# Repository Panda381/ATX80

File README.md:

# ATX80
ZX-80 computer clone with ATmega8 processor and with BASIC interpreter written in AVR assembler.

Last Update: 12/15/2021

open source

(c) Miroslav Nemecek
Panda38@seznam.cz

project home web page: http://www.breatharian.eu/hw/atx80/index_en.html

ATX80 on GitHub: https://github.com/Panda381/ATX80

License
-------
All of my software creations are distributed under the Unlicense
https://spdx.org/licenses/Unlicense.html,
and my hardware creations under the CC0 license
https://creativecommons.org/publicdomain/zero/1.0/legalcode.en.
You are free to use, modify, and distribute them for any purpose without having
to credit me as the author. The exception is content derived from third-party
sources. These third-party components are not covered by my Unlicense or CC0
licenses, but rather by the original license terms of their authors. These
components are marked in the code, and when using them, you must comply with
the terms of the original licenses.

Description
-----------
The ATX-80 is a microcomputer derived from the ZX-80, with an ATmega8 processor. It does not emulate code, but replaces the original computer with custom code with similar functionality in AVR assembly. It allows output of the video to a VGA monitor or to a PAL/NTSC television. BASIC programs can be stored in internal EEPROM, internal Flash or external EEPROM memory (32 memory slots) and also transferred between PC and memory. The advantages are easy construction and small size. It can be used as a small inexpensive computer for teaching basic BASIC programming. Includes 32 sample programs.

The original intent of the project was to create a computer with similar features and technical limitations as the original ZX-80. That is, a fully functional BASIC interpreter with only 1 KB of RAM and as close to 4 KB of ROM as possible. The project was also conceived as a study of the original ZX-80 BIOS ROM. It must be admitted that the original ZX-80 BIOS was an admirable creation. In addition to being very innovative, it was created with a high optimization of code size, and although this required a considerable amount of clarity in the flow of data between functions, the author maintained an overview of the code with minimal errors. I have tried to keep the functionality of the original code as accurate as possible and commented my code in detail, which can be a useful addition to explain the BIOS functionality. The ZX-80 BIOS is a very useful and informative study material and, despite its age, deserves more attention as an admirable work.

The ATmega8 processor was chosen to rewrite the code, which has 1 KB of RAM (the same limitation as the ZX-80) and 8 KB of Flash memory. Although the Flash memory is more than the original 4 KB, the code was about 40% longer after rewriting (AVR instructions are 16-bit) and additional functions were added, such as a more complex video generator, memory handling, 1 KB of internal Flash was used as a memory slot to store programs, so the 8 KB of memory was used efficiently.

The ATX-80 includes a keyboard of 40 micro switches. It can generate video for VGA monitor and also video in PAL and NTSC television standard via Cinch connector. It is powered by an external +5V source via USB connector (USB charger or computer connector). An external 32 KB EEPROM memory is used to store user BASIC programs, allowing 32 programs to be stored in 32 memory slots. In addition to the external EEPROM memory, one internal memory slot in the processor's Flash memory can be used to copy programs between different external EEPROM memories. The edited program is also automatically mirrored in the internal EEPROM memory. The internal EEPROM has a size of only 512 bytes, so some programs do not fit in it completely, but most programs are no larger than 512 bytes (RAM must be shared with variables and video memory) and for longer programs at least a larger part is backed up.

Advantages of the ATX-80 over the original ZX-80:
- VGA video output
- Image is generated while the program is running (FAST and SLOW modes can be used)
- Preservation of the edited program even after shutdown
- Saving programs to external EEPROM
- Autorepeat keys
- Function with memory information
- Higher program running speed
- Small size

Limitations of the ATX-80 compared to the original ZX-80:
- Cannot run programs in machine code (USR function is not functional)
- Memory cannot be increased by external memory
- Cannot connect additional devices via external bus
- The tape recorder cannot be used to store programs, only its own EEPROM memory can be used
- Generated image characters contain an extra 9th white bar (consequence of image generation by SPI port)

ZX-80 BIOS errors
-----------------
While studying the ZX-80 BIOS I came across a few minor bugs.

1) REM command error. The address of the REM routine should be L0849 instead of L084A. The error causes that giving the REM command without parameters (no text) will not execute the next line.

2) Error in the ED-EDIT routine - the following instructions should be in reverse order. The error can cause the computer to crash when writing a command when memory is full.

	JR NC,L03A7	; back to ED-COPY if not enough
			; room to fill edit line.
	POP HL		; restore program position.

3) The following error, although not apparent, is a potential risk when changing the compilation. At the beginning of the L03CB ED-EDIT routine, the initialization of register B to a value representing the number of lines to print is missing (a number of 2 or higher is needed). At this point, register B contains a value of 3 (derived from address L03CB), which is suitable, but recompiling from a different address could cause the bottom screen to stop printing. However, it is possible that the author deliberately omitted this instruction there, as part of the optimization.

Wiring diagram
--------------
The main processor is ATmega8. If necessary, it can be replaced by ATmega88, ATmega168 or ATmega328 processors, which are pin compatible. A different firmware code must be used, which is also provided in the download package. However, the larger memory of the higher processor types is not used.

The processor is driven by a 24 MHz crystal. This frequency is necessary to display the required resolution on a VGA monitor. Although the frequency of the crystal used lies above the limits declared by the manufacturer, in practice it has been found that practically all processors can handle such overclocking fine. Still, it is advisable to use a socket for the processor and try another piece of the processor in case of difficulties. Insufficient supply voltage may also be the cause of malfunction. The cutoff frequency of the processor is dependent on the power supply, a low supply voltage may cause the processor to not work properly with the crystal used.

The keyboard is wired in a 5x8 key matrix, with similar wiring to the original ZX-80, just with reverse current flow. When scanning the keyboard, signals COL1 to COL5 are wired as input (i.e., high impedance state) and only one of the COL signals is set as output with the LOW level. Signals ROW1 to ROW8 are connected as input with an internal pull-up resistor. When the keypad is scanned, one of the COL signals is activated to LOW level and the reading of the ROW signals detects the key pressed.

The MOSI output from the SPI generator is routed as a video signal to both the VGA connector and the CINCH connector for output to the TV. The output is assumed to be loaded with a 75 ohm input resistor, which will provide the required voltage level of 0.7V. The SYNC signal is the output from Timer1, which provides horizontal synchronization. Timer1 simultaneously triggers an interrupt to the video generator, which sends the video data through the SPI controller.

The VSYNC signal is only used in "old VGA display" mode. Otherwise, a CSYNC sync mix is normally generated at the SYNC output. The vertical signal is created in the sync mix by negating the horizontal sync signal. Most current VGA monitors support sync mix and work well in this mode. Only older VGA monitors require the use of a VSYNC signal as well. For most monitors, no difference between old/new VGA monitor modes should normally be observed.

The external EEPROM memory is connected via the TWI/I2C signals (SDA and SCL). A 32 KB 24LC256P memory is recommended as the most suitable type, which can hold 32 user programs (32 slots, where each slot is 1 KB in size). In addition to this, 24LC32 (4KB, i.e. 4 slots), 24LC64 (8 KB, i.e. 8 slots), 24LC128 (16 KB, i.e. 16 slots) and 24LC512 (64 KB, i.e. 64 slots) can also be used. The memories differ only in the number of available memory slots.

It is advisable to use a socket for the EEPROM memory so that it can be replaced with another one with different stored programs if necessary. Programs can be copied between memories using both the slot in the internal Flash memory and the included copy utility.

The EEPROM memories used contain a write-protect input pin. The ATX-80 does not provide for this, but a configuration jumper can be added to the board to enable or disable writing to the EEPROM memory and thus protect its contents against unwanted overwriting.

Note: The ATX-80 does not recognize the size of the attached EEPROM memory. It is up to the user to use the correct slot number. If you use a slot number outside the memory range, the slot number will be overwritten by modulo operations to another slot (EEPROM ignores unused higher address bits) and may inadvertently overwrite another stored program. For example, writing to slot 34 in a 32 KB memory will write to slot 2.

Note 2: It is assumed that the same hardware will be used for the planned ZX-81 clone, but a different processor with larger memory (probably ATmega328) will be used. Therefore, use a socket for the processor to make it easily replaceable.

Construction
------------
The ATX-80 is designed for a 100x75 mm single-sided PCB - partly because of the limitations of the freeware version of the Eagle editor, and partly because this is one of the dimensions of commonly sold photo-etch PCBs. I produce the PCB by printing the master in an inkjet printer on transparent film (gluing 2 printed master with adhesive for better coverage), illuminating with UV-LED field (10 minutes from a distance of 30 cm), exposing in potassium hydroxide and etching in ferric chloride.

Please note that in case of customised PCB production, it is necessary to check the definitions of the hole diameters in the template (I drilled the holes myself and therefore not verified).

A sticker with button labels is folded over the buttons. I printed it on regular paper on an inkjet printer, covered both sides with adhesive and then punched holes for the buttons with a 4 mm cut-out.

Programming and starting up
---------------------------
Set the fuses as follows:

ATmega8: low 0xEF (default 0xE1), high 0xC7 (default 0xD9)
ATmega88: low 0xF7 (default 0x62), high 0xD7 (default 0xDF), ext 0xFF (default 0xF9)
ATmega168: low 0xF7 (default 0x62), high 0xD7 (default 0xDF), ext 0xFF (default 0xF9)
ATmega328: low 0xF7 (default 0x62), high 0xD7 (default 0xD9), ext 0xFF (default 0xFF)

The fuses are set to map the boot loader to the smallest memory size (needed for writing to the internal flash memory), protect the internal EEPROM during programming, and fast external crystal.

If you connect a VGA monitor after programming the processor, you should see a basic white screen with a "K" cursor in the lower left corner. If this does not happen, a video mode other than the default VGA may be selected. To switch the video mode, hold down any of the buttons 1 through 4 on the keyboard while turning on the power:

- 1 + power supply: old VGA monitor (uses VSYNC signal)
- 2 + power supply: new VGA monitor (uses CSYNC sync mix)
- 3 + power supply: NTSC TV video mode (output via CINCH connector)
- 4 + power supply: PAL TV video mode (output via CINCH connector)

The selected configuration is stored in the last byte of the EEPROM memory for future use. If the video mode cannot be switched, you may have a short circuit on one of the buttons.

Be careful not to use the above operation to set the vieomode on a processor with a copy utility. It could inadvertently activate the programming of the external EEPROM.

You can check whether the processor is working without connecting the display. Insert the LED into the VGA connector between pins 14 (anode, long plus pin) and 10 (cathode, shorter minus pin). If you turn on video mode 1 (the old VGA monitor), the LED will light up (VSYNC signal is active), the LED will not light up for other video modes. Or you can plug the LED into the CINCH connector (anode to the pinhole, cathode to the shell) - if an image is being generated, the LED will light.

Programming EEPROM with sample programs
---------------------------------------
Uploading programs to EEPROM

After testing the basic functionality of the ATX-80, I recommend programming the connected external EEPROM memory. In the attachment you will find a set of utilities to load a set of 32 sample programs into the EEPROM. This requires either reprogramming the main processor or using another processor as a "copier".

In the utilities package there is a folder ATX80_Import, where you can find firmware (BIN files) for the copy processor, prepared for ATmega8/88/168/328 processors (the first number in the BIN file name indicates the processor). There are 3 sets of programs for each type of processor: slot 1 to 12, slot 13 to 24 and slot 25 to 32. The contents of the programs can be found in the utility package in the files Programs_1.txt, Programs_2.txt and Programs_3.txt. Alternatively, the program descriptions can be found in the Programs.txt file in the ATX-80 source code package.

The copy program does not use a display, but only an indicator LED to save memory. Insert it into the VGA connector on the VSYNC signal, between pins 14 (anode, long plus pin) and 10 (cathode, shorter minus pin).

Load the *_1.bin program with the first set of sample programs into the processor. The LED will flash rapidly to indicate that the processor is in a standby state. If you now press button 4 on the keypad, the LED will light steadily for a few seconds to indicate that EEPROM programming is in progress. It will then flash again quickly to indicate that the operation has been completed. Load the other 2 sets of sample programs in this manner one at a time. The button must be pressed for at least half a second to be registered - the LED must light up for at least 1 second.

Copying programs between EEPROMs

The program set in the utility package is also used to download or copy programs from the external EEPROM memory. Use the following procedure to copy the contents of the EEPROM to another memory.

Load the program from the ATX80_Copy folder for the corresponding processor into the processor. The LED will flash to indicate readiness. Press any of the buttons 1 through 3. The LED will light momentarily to indicate an operation in progress, and the programs from the EEPROM will be downloaded to the processor's internal Flash memory. The button determines which slots are downloaded. Button 1 downloads slots 1 through 11, button 2 downloads slots 12 through 22, and button 3 downloads slots 23 through 32. Theoretically, the ATmega8 may not fit 11 slots - they would mean 11 KB of memory, but the ATmega8 has only 8 KB. In practice, most programs are smaller so they can fit into 8 KB. If sometimes they don't, you would need to use a processor with more memory or adjust the slot counts in the copy program source code.

After downloading the programs to the processor, turn off the power, replace the EEPROM memory, and turn on the power. Press button 4 to save the loaded programs from Flash memory to the new external EEPROM memory. All programs that are in memory are saved and stored in the same slots from which they were downloaded.

Download programs from EEPROM

You can also download programs to your PC using utilities. First, as in the previous case, download the appropriate set of programs to the processor's Flash memory (using buttons 1 to 3). Connect the CPU programmer and download the CPU Flash memory to the ATX80_Copy folder, to files named 1.bin to 3.bin. In the ATX80_Export folder, run the command file !.bat. This will export the programs from the downloaded Flash memory images to the text files Programs_1.txt through Programs_3.txt in the base utilities folder. Within the files, you can edit the downloaded files in text form. Each program code is prefixed with a "SLOT x" to indicate which slot the program belongs to. The label indicates the start of the program for further processing. All subsequent lines starting with a number are processed as program lines. Program lines may be followed by LET or DIM statements containing the filling of numeric or text variables.

If you wish to load programs in text form back into EEPROM, run the !.bat command file in the ATX80_Import folder. This will ensure that the programs from the text form are imported back into the copy program images. Then all you have to do is load the programs into the processor and press button 4 to save them to the external EEPROM, just as described at the beginning of this chapter.

Description of the ATX-80 BASIC
-------------------------------
The ATX-80 BASIC is almost completely identical to the ZX-80 BASIC, except for a few small differences.

The program line number can range from 1 to 9999. After each change in program lines, the program is automatically backed up to the internal EEPROM. The internal EEPROM has a capacity of only 510 bytes and therefore may not hold the entire program. When the ATX-80 is turned on, the program stored in the internal EEPROM is restored.

The BASIC ATX-80 operates with integers in the range -32768 to +32767. Variables can be of the following types:

- an integer variable with an arbitrarily long name (starts with a letter, can be followed by letters or digits)
- an integer variable with only 1 letter can be used as a FOR loop parameter
- text variable is 1 letter followed by $, text can be of any length
- the array is 1 letter, the array index can be 255 max

Operations:

+ "+" "-" ... sum and difference
+ "*" "/" ... multiplication and division (integer only)
+ AND ... bitwise and logical product
+ OR ... bitwise and logical sum
+ NOT ... bitwise and logical inverse
+ "**" ... power
+ "=" ... comparison of numbers and texts for equality
+ "<" ... comparison of numbers and texts to smaller
+ ">" ... comparison of numbers and texts to greater

Commands, they can be only at the beginning of the line or after the THEN command, they are called by pressing a letter:

+ LIST ... (A) program listing from the specified line, without entering the line number listing from the beginning
+ RETURN ... (B) return from procedure
+ CLS ... (C) clearing the screen
+ DIM ... (D) array declaration. The array may begin with index 0. The maximum size of the array is 255 (e.g., DIM A(255), indices can be 0 to 255.
+ SAVE ... (E) save the program and variables into the slot. This is followed by slot number 1 to 32 for external EEPROM. Without entering a number or by entering a number 0, the program and variables are stored in the processor's internal Flash memory.
+ FOR ... (F) loop, followed by a 1-letter variable with a starting value, followed by a TO with an ending value.
+ GO TO ... (G) jump to the specified line number
+ POKE ... (H) store a byte in RAM, followed by the address and contents of the byte. The ATX-80 simulates storing into RAM addresses identical to the ZX-80.
+ INPUT ... (I) user input, followed by the destination numeric or text variable
+ RANDOMISE ... (J) initialization of the random generator by a specified number, entering 0 or omitting a parameter initializes according to the frame counter
+ LET ... (K) setting the content of the variable
+ FAST ... (L) setting the fast mode, only 1 top line is displayed and the processor is sped up 4 times. Can only be used while the program is running.
+ SLOW ... (M) fast mode setting, full screen will be displayed. Set automatically when the program is exited.
+ NEXT ... (N) continue cycle for the specified variable
+ PRINT ... (O) printout of variables or text. The ';' character ensures continuation without a space, the ',' character is indented after 8-character tab positions.
+ MEMORY ... (P) lists memory information in bytes: program size, variable size, and free RAM space.
+ NEW ... (Q) erases the program and variables
+ RUN ...(R) runs the program from the specified line. Without specifying a line number, the program starts from the beginning. At the same time, it clears the variables.
+ STOP ... (S) stops the program. You can continue with the CONTINUE command.
+ CONTINUE ... (T) resume the program from the interruption with the STOP command.
+ IF ... (U) condition. THEN is followed by the statement executed when the condition or expression is valid (the expression is valid if non-zero).
+ GO SUB .. (V) jump to a procedure. From the procedure, the RETURN statement returns to the line following GO SUB.
+ LOAD ... (W) Load the program and variables from the slot. This is followed by the slot number 1 to 32 for the external EEPROM. Without entering a number or by entering number 0, the program and variables are loaded from the processor's internal Flash memory.
+ CLEAR ... (X) clear variables
+ REM ... (Y) comment

Functions and other commands (functions must be written in text, they do not have a keyboard shortcut):

+ " ... (Shift+Y) indicates the beginning and end of the text
+ THEN ... (Shift+3) part of the IF condition, indicates the command executed when the condition is met
+ TO ... (Shift+4) part of a FOR loop, indicates the end value of a variable
+ ";" ... (Shift+Z) part of the PRINT statement, continues printing from the last position
+ "," ... (Shift+.) part of the PRINT statement, continue printing from the tabular position
+ "(" ")" ... (Shift+I, Shift+O) brackets
+ PEEK ... Load the contents of memory from the address specified in the brackets. The ATX-80 simulates RAM addresses identical to the ZX-80, including the font address in ROM. The contents of pointers are not simulated; these must be recalculated.
+ CHR$ ... converting a character code to a text character
+ CODE ... conversion of a text character (first character of text) to a numeric code
+ RND ... random generator, generates a number from 1 to the specified maximum number
+ TL$ ... returns the text without the first character
+ USR ... not supported in ATX-80
+ STR$ ... converts number to text
+ ABS ... absolute value of number

Sample programs
---------------
Sample programs are stored in the external EEPROM in slots 1 to 32. The contents of the EEPROM can be copied to another EEPROM, downloaded to the PC, or loaded from the PC into the EEPROM as described in the EEPROM Programming chapter.

The contents of the programs can be found in the Programs.txt file in the source code, along with their detailed descriptions.

1) Print charset
2) High precision division
3) Square root routine
4) Die throwing
5) Reaction timer
6) Histogram of random number
7) Leap frog
8) Message encoding
9) Horse Race
10) Lunar Lander (run with GO TO 100)
11) Maze generator
12) Noughts and Crosses (Tic Tac Toe)
13) Dr. ATX80 - psycho therapist (run with GO TO 120)
14) NIM game (taking matches)
15) Blackjack
16) Bubble sort
17) Line renumber (run with GO TO 9987)
18) Draw a picture (restore saved picture with GO TO 200)
19) Calculate day of the week
20) Chinese remainder
21) Simple Simon - write letters
22) Hangman - guess letters
23) Maths drill - learn addition and subtraction
24) Learn capitals of the World
25) Life - cellular automaton
26) Prime number generator
27) Simultaneous equations
28) Square root to 3 decimal places
29) Pontoon (cards)
30) Chomp (game - take grid)
31) Mastermind (game - guess digits)
32) Pinch (game - capture oponent)

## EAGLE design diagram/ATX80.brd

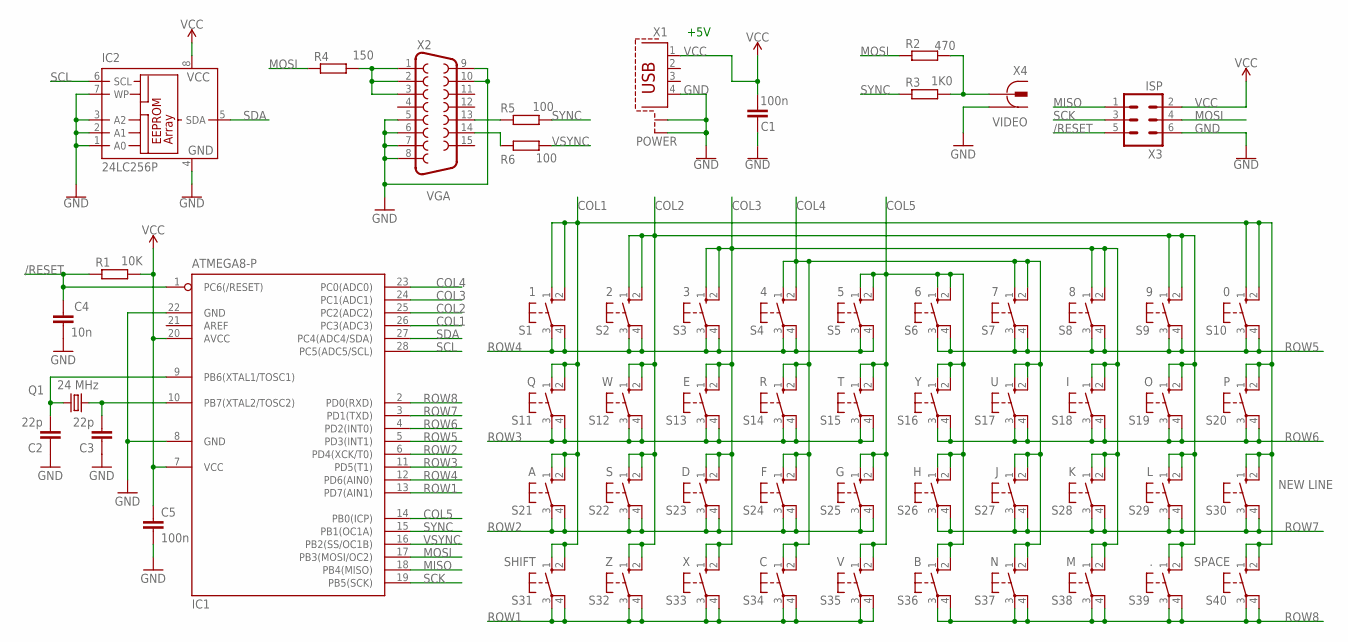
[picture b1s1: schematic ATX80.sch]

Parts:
C1, C5: 100n; C050-024X044
C2, C3: 22p; C050-024X044
C4: 10n; C050-024X044
IC1: ATMEGA8-P; DIL28-3
IC2: 24LC256P; DIL8
Q1: 24 MHz; HC49U-V
R1: 10K; 0204/7
R2: 470; 0204/7
R3: 1K0; 0204/7
R4: 150; 0204/7
R5, R6: 100; 0204/7
S1: 1; B3F-10XX
S2: 2; B3F-10XX
S3: 3; B3F-10XX
S4: 4; B3F-10XX
S5: 5; B3F-10XX
S6: 6; B3F-10XX
S7: 7; B3F-10XX
S8: 8; B3F-10XX
S9: 9; B3F-10XX
S10: 0; B3F-10XX
S11: Q; B3F-10XX
S12: W; B3F-10XX
S13: E; B3F-10XX
S14: R; B3F-10XX
S15: T; B3F-10XX
S16: Y; B3F-10XX
S17: U; B3F-10XX
S18: I; B3F-10XX
S19: O; B3F-10XX
S20: P; B3F-10XX
S21: A; B3F-10XX
S22: S; B3F-10XX
S23: D; B3F-10XX
S24: F; B3F-10XX
S25: G; B3F-10XX
S26: H; B3F-10XX
S27: J; B3F-10XX
S28: K; B3F-10XX
S29: L; B3F-10XX
S30: NEW LINE; B3F-10XX
S31: SHIFT; B3F-10XX
S32: Z; B3F-10XX
S33: X; B3F-10XX
S34: C; B3F-10XX
S35: V; B3F-10XX
S36: B; B3F-10XX
S37: N; B3F-10XX
S38: M; B3F-10XX
S39: .; B3F-10XX
S40: SPACE; B3F-10XX
X1: POWER; PN61729-S
X2: VGA; HDF15H
X3: ISP; ML6L
X4: VIDEO; 736880-49

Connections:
/RESET: C4.1, IC1.1 (PC6(/RESET)), R1.1, X3.5
COL1: IC1.26 (PC3(ADC3)), S1.1 (S), S1.2 (S1), S10.1 (S), S10.2 (S1), S11.1 (S), S11.2 (S1), S20.1 (S), S20.2 (S1), S21.1 (S), S21.2 (S1), S30.1 (S), S30.2 (S1), S31.1 (S), S31.2 (S1), S40.1 (S), S40.2 (S1)
COL2: IC1.25 (PC2(ADC2)), S2.1 (S), S2.2 (S1), S9.1 (S), S9.2 (S1), S12.1 (S), S12.2 (S1), S19.1 (S), S19.2 (S1), S22.1 (S), S22.2 (S1), S29.1 (S), S29.2 (S1), S32.1 (S), S32.2 (S1), S39.1 (S), S39.2 (S1)
COL3: IC1.24 (PC1(ADC1)), S3.1 (S), S3.2 (S1), S8.1 (S), S8.2 (S1), S13.1 (S), S13.2 (S1), S18.1 (S), S18.2 (S1), S23.1 (S), S23.2 (S1), S28.1 (S), S28.2 (S1), S33.1 (S), S33.2 (S1), S38.1 (S), S38.2 (S1)
COL4: IC1.23 (PC0(ADC0)), S4.1 (S), S4.2 (S1), S7.1 (S), S7.2 (S1), S14.1 (S), S14.2 (S1), S17.1 (S), S17.2 (S1), S24.1 (S), S24.2 (S1), S27.1 (S), S27.2 (S1), S34.1 (S), S34.2 (S1), S37.1 (S), S37.2 (S1)
COL5: IC1.14 (PB0(ICP)), S5.1 (S), S5.2 (S1), S6.1 (S), S6.2 (S1), S15.1 (S), S15.2 (S1), S16.1 (S), S16.2 (S1), S25.1 (S), S25.2 (S1), S26.1 (S), S26.2 (S1), S35.1 (S), S35.2 (S1), S36.1 (S), S36.2 (S1)
GND: C1.1, C2.1, C3.1, C4.2, C5.2, IC1.8 (GND), IC1.22 (GND), IC2.1 (A0), IC2.2 (A1), IC2.3 (A2), IC2.4 (GND), IC2.7 (WP), X1.4, X1.S1, X1.S2, X2.5, X2.6, X2.7, X2.8, X2.9, X2.10, X3.6, X4.1, X4.1@1 (1), X4.1@2 (1)
MISO: IC1.18 (PB4(MISO)), X3.1
MOSI: IC1.17 (PB3(MOSI/OC2)), R2.1, R4.1, X3.4
unnamed: R6.1, X2.14
unnamed: R5.1, X2.13
unnamed: R4.2, X2.1, X2.2, X2.3
unnamed: C2.2, IC1.9 (PB6(XTAL1/TOSC1)), Q1.2
unnamed: C3.2, IC1.10 (PB7(XTAL2/TOSC2)), Q1.1
unnamed: R2.2, R3.2, X4.2
ROW1: IC1.13 (PD7(AIN1)), S31.3, S31.4 (P1), S32.3, S32.4 (P1), S33.3, S33.4 (P1), S34.3, S34.4 (P1), S35.3, S35.4 (P1)
ROW2: IC1.6 (PD4(XCK/T0)), S21.3, S21.4 (P1), S22.3, S22.4 (P1), S23.3, S23.4 (P1), S24.3, S24.4 (P1), S25.3, S25.4 (P1)
ROW3: IC1.11 (PD5(T1)), S11.3, S11.4 (P1), S12.3, S12.4 (P1), S13.3, S13.4 (P1), S14.3, S14.4 (P1), S15.3, S15.4 (P1)
ROW4: IC1.12 (PD6(AIN0)), S1.3, S1.4 (P1), S2.3, S2.4 (P1), S3.3, S3.4 (P1), S4.3, S4.4 (P1), S5.3, S5.4 (P1)
ROW5: IC1.5 (PD3(INT1)), S6.3, S6.4 (P1), S7.3, S7.4 (P1), S8.3, S8.4 (P1), S9.3, S9.4 (P1), S10.3, S10.4 (P1)
ROW6: IC1.4 (PD2(INT0)), S16.3, S16.4 (P1), S17.3, S17.4 (P1), S18.3, S18.4 (P1), S19.3, S19.4 (P1), S20.3, S20.4 (P1)
ROW7: IC1.3 (PD1(TXD)), S26.3, S26.4 (P1), S27.3, S27.4 (P1), S28.3, S28.4 (P1), S29.3, S29.4 (P1), S30.3, S30.4 (P1)
ROW8: IC1.2 (PD0(RXD)), S36.3, S36.4 (P1), S37.3, S37.4 (P1), S38.3, S38.4 (P1), S39.3, S39.4 (P1), S40.3, S40.4 (P1)
SCK: IC1.19 (PB5(SCK)), X3.3
SCL: IC1.28 (PC5(ADC5/SCL)), IC2.6 (SCL)
SDA: IC1.27 (PC4(ADC4/SDA)), IC2.5 (SDA)
SYNC: IC1.15 (PB1(OC1A)), R3.1, R5.2
VCC: C1.2, C5.1, IC1.7 (VCC), IC1.20 (AVCC), IC2.8 (VCC), R1.2, X1.1, X3.2
VSYNC: IC1.16 (PB2(SS/OC1B)), R6.2

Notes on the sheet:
+5V

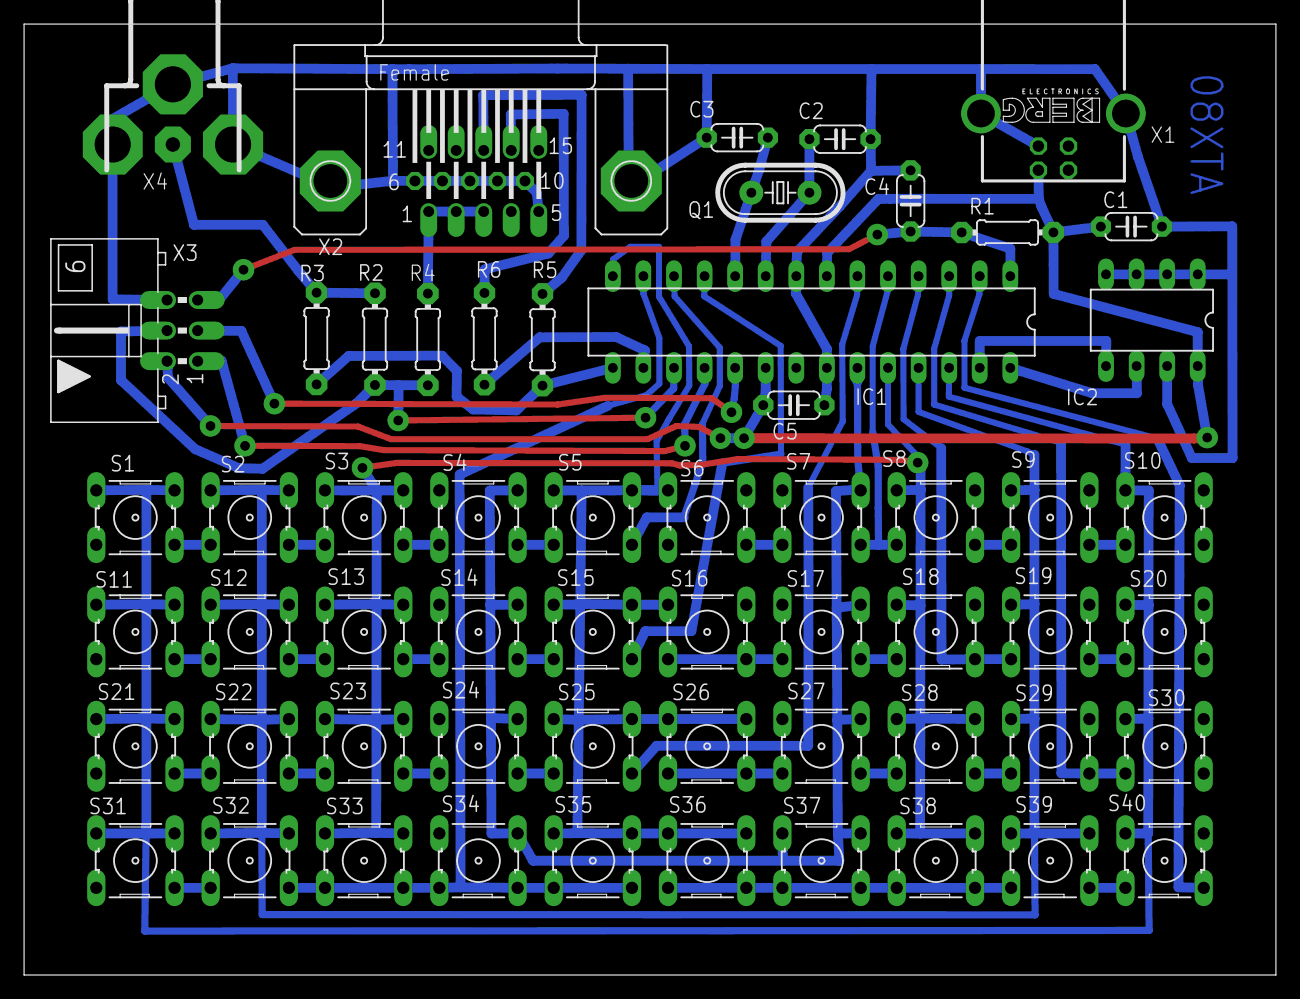
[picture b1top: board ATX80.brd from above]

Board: 2 copper layers, 104.0 x 79.0 mm, 58 parts (0 on the bottom side), 29 nets.

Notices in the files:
parts and their libraries:
SparkFun-PowerSymbols: Licensing: Creative Commons ShareAlike 4.0 International - https://creativecommons.org/licenses/by-sa/4.0
